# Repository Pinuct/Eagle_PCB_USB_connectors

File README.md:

# Eagle PCB USB connectors
Eagle library for USB connectors directly on PCB.

This repository contains documentation and a library to use with Eagle to create USB connectors directly on the PCB itself (free connectors!). By the moment the only usb connectors are the USB micro B and the USB type C. This only works with PCB thickness of 0.6 mm. 

The [eagle_library](https://github.com/Pinuct/Eagle_PCB_USB_connectors/tree/master/eagle_library) folder contains the Eagle library

The [Connector Test](https://github.com/Pinuct/Eagle_PCB_USB_connectors/tree/master/Connector%20Test) folder contains and eagle proyect of the test PCB i used to test the different models of USB pcb patterns i made.

The [micro USB type b](https://github.com/Pinuct/Eagle_PCB_USB_connectors/tree/master/micro%20USB%20type%20b)and [micro USB type c](https://github.com/Pinuct/Eagle_PCB_USB_connectors/tree/master/micro%20USB%20type%20c) folders contains documentation i used to make this proyect, it includes the PDFs of the USB spefication of each type of USB with all the data, dimensions and pinout i used to create the Eagle components. Also includes the images os the dimensions an pinout extracted form the PDF.

## Why?

I started this proyect because i wanted an easy and cheap method to connect my electronic boards to a PC. I don't wanted a realiable connector for thousands of uses, i wanted just an ocasional connector to hook up to my PC and program it, or take some data. So this type of connector are just fine for that pruporse, not soldering, not extra cost, not uncommon cables, just a mirco B cable and your are good to go. The only problem with this type of connectors is that you have to use 0.6 mm PCB thicknes, and today mosts PCB fabs can do 0.6mm thicknes without extra cost. If you are ok with that, there we go!

## Extra info

<center>
  
| USB micro B mid plate dimensions  | USB type C mid plate dimensions |
| ------------- | ------------- |
|   |   |

</center>

As you can see, both mid plates have 0.6 mm thickness. Is true that the pads itself are not below or above that dimension, but the diference is so small it doesent matter. So 0.6mm thinckes PCB and we are fine.

  In the library there are three components:

  - **PCB_MICRO_USB_B** 
  - **PCB_USB_C**   
  - **PCB_USB_C_2.0** 
  
In PCB_MICRO_USB_B there is pads only in one side (it can't be both sides because the USB plug in the micro B cable has a metalic back and it can short the pads). In the other hand, the USB type C is created to inset either way so PCB_USB_C and PCB_USB_C_2.0 has pads on both sides.
  
The difference between the PCB_USB_C and the PCB_USB_C_2.0 is that the PCB_USB_C_2.0 has extra wires and vias to convert the PCB_USB_C into a USB 2.0 specification compatible, that means that you only use 4 lines of the connector: V+, GND, D- and D+. 
  
Each one of the components have different footprint models. The difference in the models is in the cutout slots for the usb cable plug to insert on the PCB, i played with the thicknes of the slot and the terminations. I can say that in the PCB_MICRO_USB_B the one that work for me the best is the one with the tighter dimensions with the round end to give the connector a little bit more space to insert further inside. For the PCB_USB_C/2.0 i can't say which one is the best because i couldn't test it yet.
  
**USB micro B footprints:**

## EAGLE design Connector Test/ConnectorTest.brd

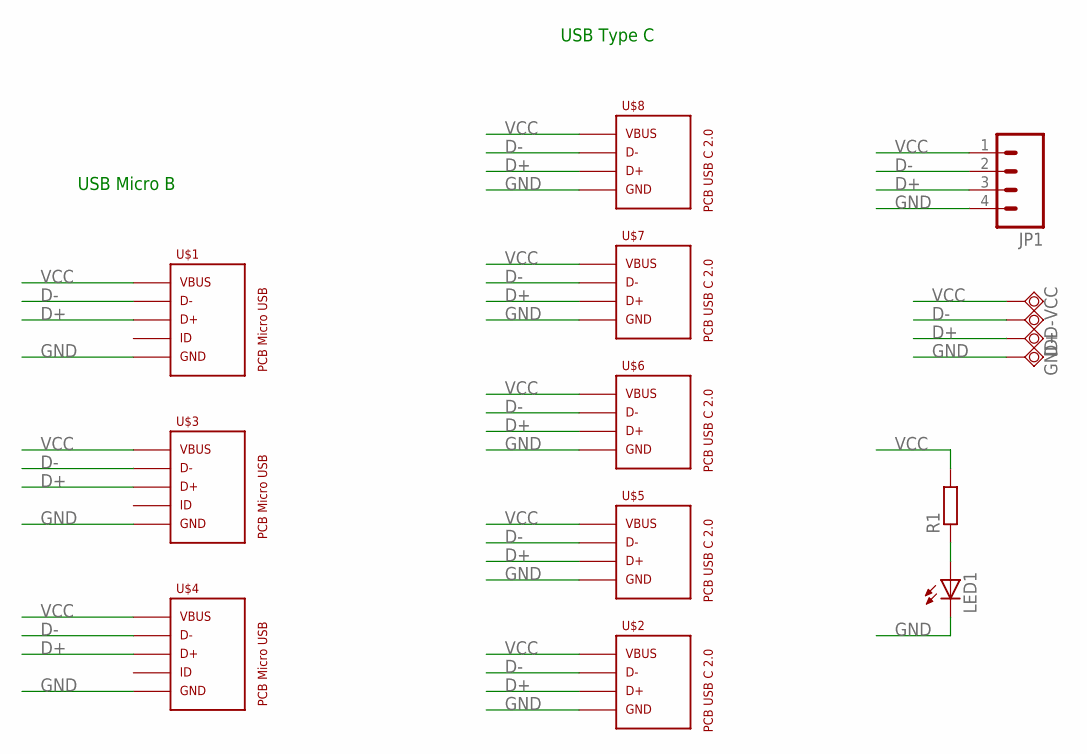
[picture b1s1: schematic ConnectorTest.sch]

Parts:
D+: TPSQTP20SQ; TP20SQ
D-: TPSQTP20SQ; TP20SQ
GND: TPSQTP20SQ; TP20SQ
JP1: M04LONGPADS; 1X04_LONGPADS
LED1: LEDSMT1206; 1206
R1: R-EU_R1206; R1206
U$1: PCB_MICRO_USB_BDSW_2; USB_TYPE_B_DSW_2
U$2: PCB_USB_C_2.0W_1; USB_TYPE_C_W_2.0_1
U$3: PCB_MICRO_USB_BDSW_3; USB_TYPE_B_DSW_3
U$4: PCB_MICRO_USB_BDSW_1; USB_TYPE_B_DSW_1
U$5: PCB_USB_C_2.0W_2; USB_TYPE_C_W_2.0_2
U$6: PCB_USB_C_2.0W_3; USB_TYPE_C_W_2.0_3
U$7: PCB_USB_C_2.0W_4; USB_TYPE_C_W_2.0_4
U$8: PCB_USB_C_2.0W_5; USB_TYPE_C_W_2.0_5
VCC: TPSQTP20SQ; TP20SQ

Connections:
D+: D+.TP, JP1.3, U$1.3D (3), U$2.D+, U$3.3D (3), U$4.3D (3), U$5.D+, U$6.D+, U$7.D+, U$8.D+
D-: D-.TP, JP1.2, U$1.2D (2), U$2.D-, U$3.2D (2), U$4.2D (2), U$5.D-, U$6.D-, U$7.D-, U$8.D-
GND: GND.TP, JP1.4, LED1.C, U$1.5D (5), U$2.GND, U$3.5D (5), U$4.5D (5), U$5.GND, U$6.GND, U$7.GND, U$8.GND
unnamed: LED1.A, R1.1
VCC: JP1.1, R1.2, U$1.1D (1), U$2.VBUS, U$3.1D (1), U$4.1D (1), U$5.VBUS, U$6.VBUS, U$7.VBUS, U$8.VBUS, VCC.TP

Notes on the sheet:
USB Micro B
USB Type C

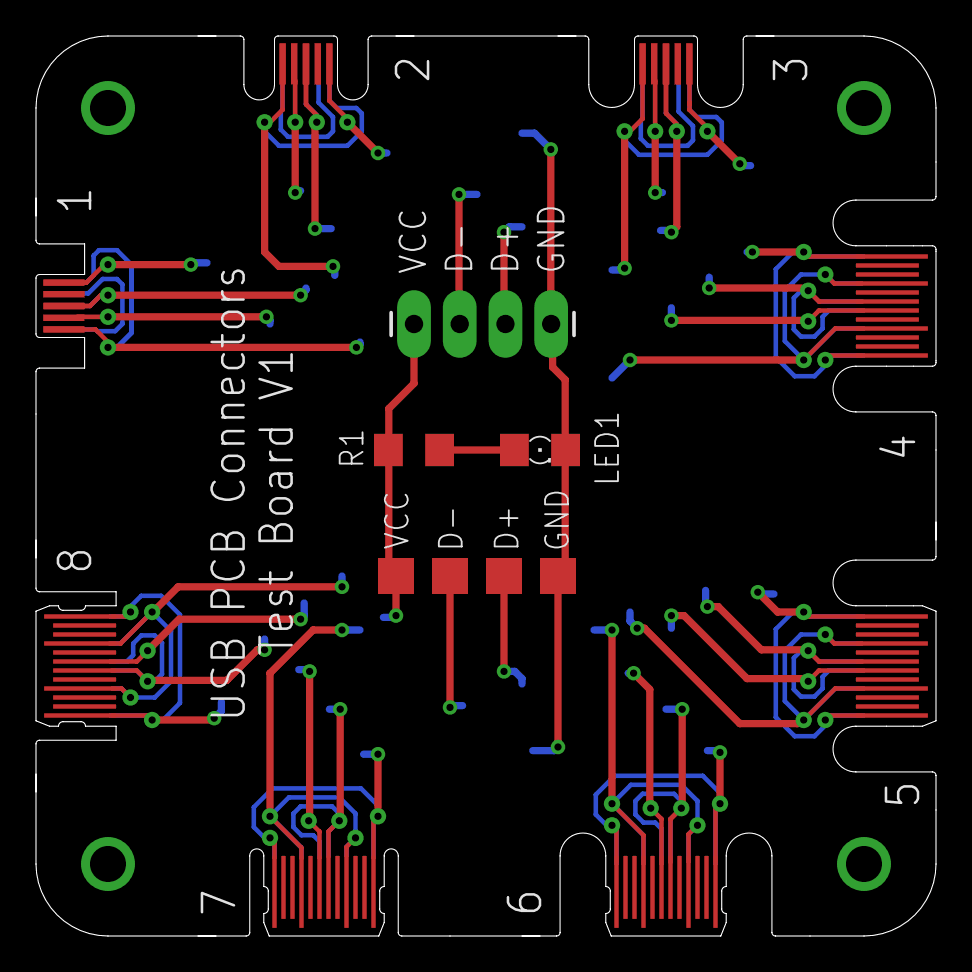
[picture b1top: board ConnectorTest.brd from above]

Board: 2 copper layers, 50.0 x 50.0 mm, 15 parts (0 on the bottom side), 5 nets.

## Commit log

2017-11-18 Initial commit, added files
2017-12-09 Deleted USB micro b double side footprints. Added footprint reference image

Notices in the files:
README.md:
License: CC BY 4.0
parts and their libraries:
01_SparkFun: Licensing: CC v3.0 Share-Alike You are welcome to use this library for commercial purposes.
